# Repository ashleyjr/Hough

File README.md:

Hough
=====

Hough transform experiment

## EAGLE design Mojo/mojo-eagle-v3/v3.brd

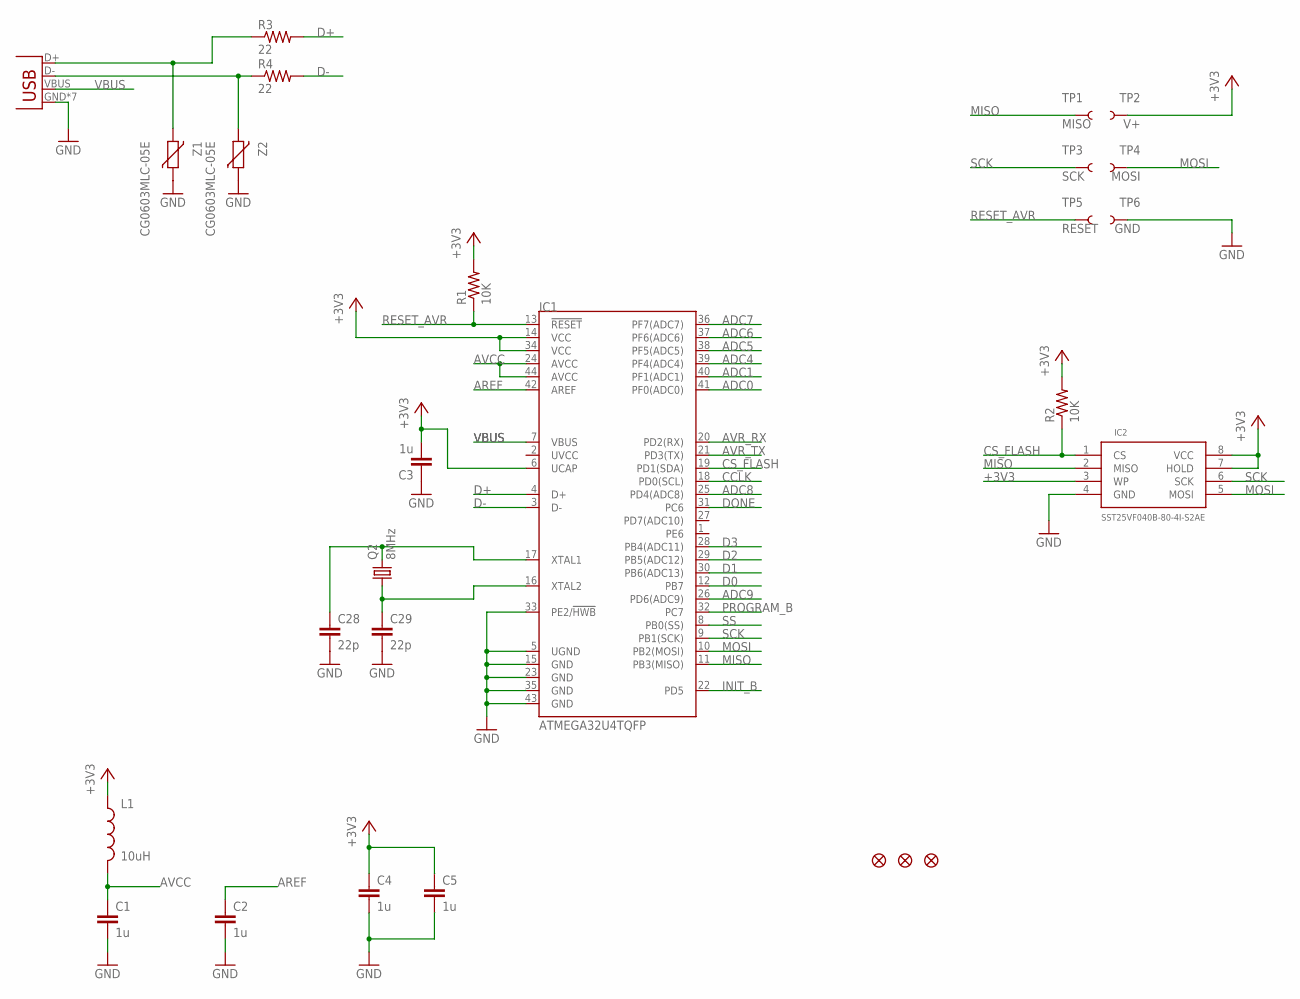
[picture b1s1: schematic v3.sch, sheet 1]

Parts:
C1, C2, C3, C4, C5: 1u; C0603K
C28, C29: 22p; C0603K
IC1: ATMEGA32U4TQFP; SPARKFUN-DIGITALIC_TQFP44
IC2: SST25VF040B-80-4I-S2AE; SO08-EIAJ
JP3, JP4, JP5: FIDUCIAL1X2; FIDUCIAL-1X2
L1: 10uH; 0603
Q2: 8MHz; ABM2
R1, R2: 10K; R0603
R3, R4: 22; R0603
TP1: MISO; PAD.03X.05
TP2: V+; PAD.03X.05
TP3: SCK; PAD.03X.05
TP4: MOSI; PAD.03X.05
TP5: RESET; PAD.03X.05
TP6: GND; PAD.03X.05
X1: USB-MICROB
Z1, Z2: CG0603MLC-05E; CT/CN0603

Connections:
+3V3: C3.2, C4.1, C5.1, IC1.6 (UCAP), IC1.14 (VCC), IC1.34 (VCC), IC2.3 (WP), IC2.7 (HOLD), IC2.8 (VCC), L1.1, R1.2, R2.2, TP2.P$1; also elsewhere on the board
ADC0: IC1.41 (PF0(ADC0)); also elsewhere on the board
ADC1: IC1.40 (PF1(ADC1)); also elsewhere on the board
ADC4: IC1.39 (PF4(ADC4)); also elsewhere on the board
ADC5: IC1.38 (PF5(ADC5)); also elsewhere on the board
ADC6: IC1.37 (PF6(ADC6)); also elsewhere on the board
ADC7: IC1.36 (PF7(ADC7)); also elsewhere on the board
ADC8: IC1.25 (PD4(ADC8)); also elsewhere on the board
ADC9: IC1.26 (PD6(ADC9)); also elsewhere on the board
AREF: C2.1, IC1.42 (AREF); also elsewhere on the board
AVCC: C1.1, IC1.24 (AVCC), IC1.44 (AVCC), L1.2
AVR_RX: IC1.20 (PD2(RX)); also elsewhere on the board
AVR_TX: IC1.21 (PD3(TX)); also elsewhere on the board
CCLK: IC1.18 (PD0(SCL)); also elsewhere on the board
CS_FLASH: IC1.19 (PD1(SDA)), IC2.1 (CS), R2.1
D0: IC1.12 (PB7); also elsewhere on the board
D1: IC1.30 (PB6(ADC13)); also elsewhere on the board
D2: IC1.29 (PB5(ADC12)); also elsewhere on the board
D3: IC1.28 (PB4(ADC11)); also elsewhere on the board
D+: IC1.4 (D+), R3.2
D-: IC1.3 (D-), R4.2
DONE: IC1.31 (PC6); also elsewhere on the board
GND: C1.2, C2.2, C3.1, C4.2, C5.2, C28.2, C29.2, IC1.5 (UGND), IC1.15 (GND), IC1.23 (GND), IC1.33 (PE2/!HWB), IC1.35 (GND), IC1.43 (GND), IC2.4 (GND), TP6.P$1, X1.GND, X1.P1 (GND), X1.P2 (GND), X1.P3 (GND), X1.P4 (GND), X1.P5 (GND), X1.P6 (GND), Z1.1, Z2.1; also elsewhere on the board
INIT_B: IC1.22 (PD5); also elsewhere on the board
MISO: IC1.11 (PB3(MISO)), IC2.2 (MISO), TP1.P$1; also elsewhere on the board
MOSI: IC1.10 (PB2(MOSI)), IC2.5 (MOSI), TP4.P$1; also elsewhere on the board
unnamed: R3.1, X1.D+, Z1.2
unnamed: R4.1, X1.D-, Z2.2
unnamed: C28.1, IC1.17 (XTAL1), Q2.P$2 (2)
unnamed: C29.1, IC1.16 (XTAL2), Q2.P$1 (1)
PROGRAM_B: IC1.32 (PC7); also elsewhere on the board
RESET_AVR: IC1.13 (!RESET), R1.1, TP5.P$1
SCK: IC1.9 (PB1(SCK)), IC2.6 (SCK), TP3.P$1; also elsewhere on the board
SS: IC1.8 (PB0(SS)); also elsewhere on the board
VBUS: IC1.7 (VBUS), X1.VBUS; also elsewhere on the board

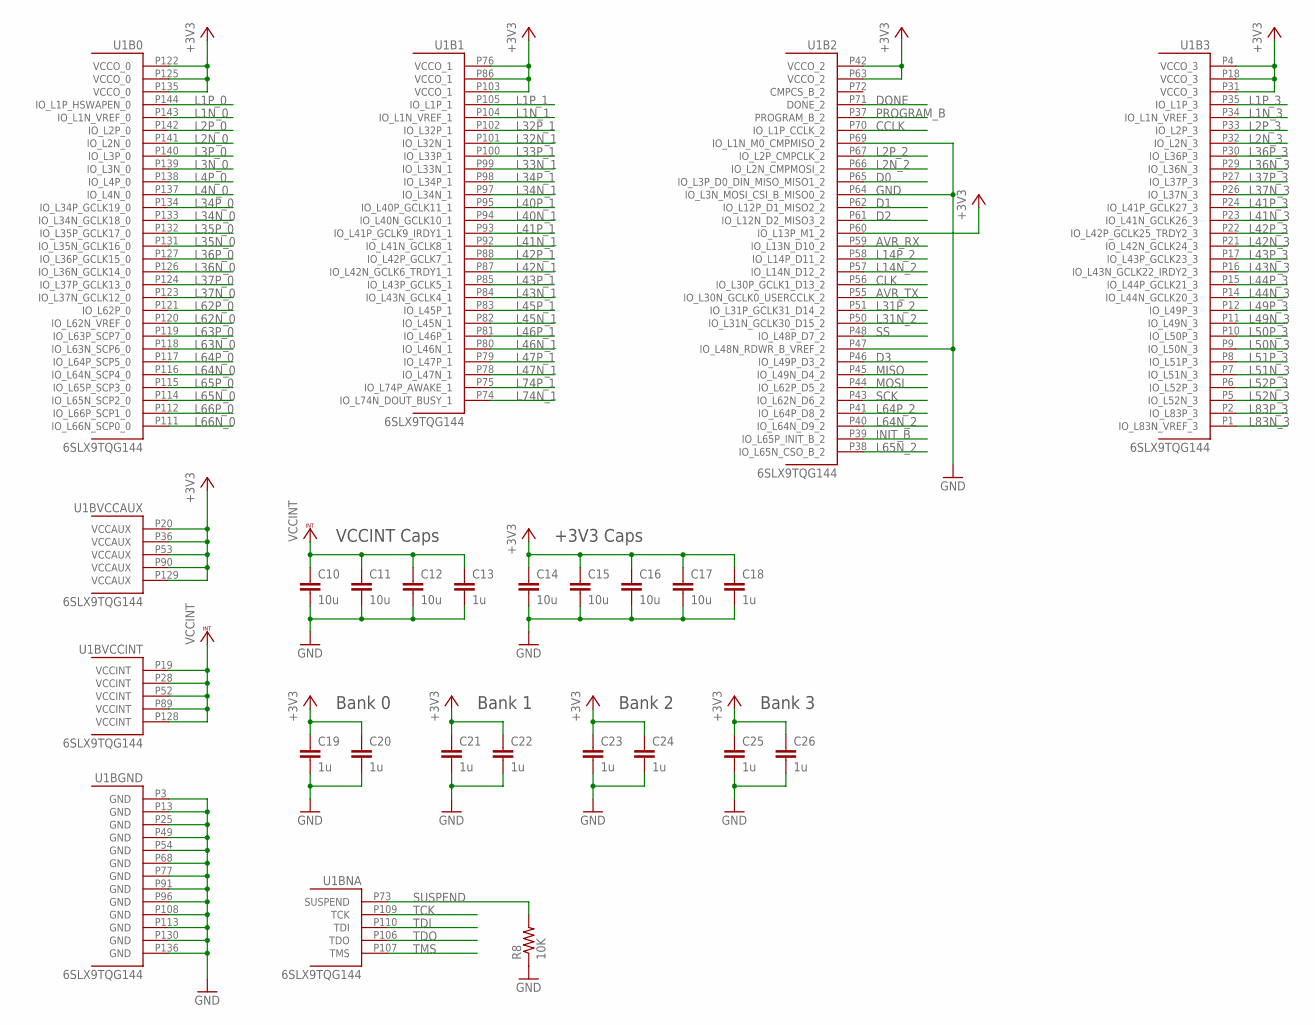
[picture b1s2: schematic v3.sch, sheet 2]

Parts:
C10, C11, C12, C14, C15, C16, C17: 10u; C0603K
C13, C18, C19, C20, C21, C22, C23, C24, C25, C26: 1u; C0603K
R8: 10K; R0603
U1: 6SLX9TQG144; TQ144

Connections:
+3V3: C14.1, C15.1, C16.1, C17.1, C18.1, C19.1, C20.1, C21.1, C22.1, C23.1, C24.1, C25.1, C26.1, U1.P4 (VCCO_3), U1.P18 (VCCO_3), U1.P20 (VCCAUX), U1.P31 (VCCO_3), U1.P36 (VCCAUX), U1.P42 (VCCO_2), U1.P53 (VCCAUX), U1.P60 (IO_L13P_M1_2), U1.P63 (VCCO_2), U1.P76 (VCCO_1), U1.P86 (VCCO_1), U1.P90 (VCCAUX), U1.P103 (VCCO_1), U1.P122 (VCCO_0), U1.P125 (VCCO_0), U1.P129 (VCCAUX), U1.P135 (VCCO_0); also elsewhere on the board
AVR_RX: U1.P59 (IO_L13N_D10_2); also elsewhere on the board
AVR_TX: U1.P55 (IO_L30N_GCLK0_USERCCLK_2); also elsewhere on the board
CCLK: U1.P70 (IO_L1P_CCLK_2); also elsewhere on the board
CLK: U1.P56 (IO_L30P_GCLK1_D13_2); also elsewhere on the board
D0: U1.P65 (IO_L3P_D0_DIN_MISO_MISO1_2); also elsewhere on the board
D1: U1.P62 (IO_L12P_D1_MISO2_2); also elsewhere on the board
D2: U1.P61 (IO_L12N_D2_MISO3_2); also elsewhere on the board
D3: U1.P46 (IO_L49P_D3_2); also elsewhere on the board
DONE: U1.P71 (DONE_2); also elsewhere on the board
GND: C10.2, C11.2, C12.2, C13.2, C14.2, C15.2, C16.2, C17.2, C18.2, C19.2, C20.2, C21.2, C22.2, C23.2, C24.2, C25.2, C26.2, R8.1, U1.P3 (GND), U1.P13 (GND), U1.P25 (GND), U1.P47 (IO_L48N_RDWR_B_VREF_2), U1.P49 (GND), U1.P54 (GND), U1.P64 (IO_L3N_MOSI_CSI_B_MISO0_2), U1.P68 (GND), U1.P69 (IO_L1N_M0_CMPMISO_2), U1.P77 (GND), U1.P91 (GND), U1.P96 (GND), U1.P108 (GND), U1.P113 (GND), U1.P130 (GND), U1.P136 (GND); also elsewhere on the board
INIT_B: U1.P39 (IO_L65P_INIT_B_2); also elsewhere on the board
L1N_0: U1.P143 (IO_L1N_VREF_0); also elsewhere on the board
L1N_1: U1.P104 (IO_L1N_VREF_1); also elsewhere on the board
L1N_3: U1.P34 (IO_L1N_VREF_3); also elsewhere on the board
L1P_0: U1.P144 (IO_L1P_HSWAPEN_0); also elsewhere on the board
L1P_1: U1.P105 (IO_L1P_1); also elsewhere on the board
L1P_3: U1.P35 (IO_L1P_3); also elsewhere on the board
L2N_0: U1.P141 (IO_L2N_0); also elsewhere on the board
L2N_2: U1.P66 (IO_L2N_CMPMOSI_2); also elsewhere on the board
L2N_3: U1.P32 (IO_L2N_3); also elsewhere on the board
L2P_0: U1.P142 (IO_L2P_0); also elsewhere on the board
L2P_2: U1.P67 (IO_L2P_CMPCLK_2); also elsewhere on the board
L2P_3: U1.P33 (IO_L2P_3); also elsewhere on the board
L3N_0: U1.P139 (IO_L3N_0); also elsewhere on the board
L3P_0: U1.P140 (IO_L3P_0); also elsewhere on the board
L4N_0: U1.P137 (IO_L4N_0); also elsewhere on the board
L4P_0: U1.P138 (IO_L4P_0); also elsewhere on the board
L14N_2: U1.P57 (IO_L14N_D12_2); also elsewhere on the board
L14P_2: U1.P58 (IO_L14P_D11_2); also elsewhere on the board
L31N_2: U1.P50 (IO_L31N_GCLK30_D15_2); also elsewhere on the board
L31P_2: U1.P51 (IO_L31P_GCLK31_D14_2); also elsewhere on the board
L32N_1: U1.P101 (IO_L32N_1); also elsewhere on the board
L32P_1: U1.P102 (IO_L32P_1); also elsewhere on the board
L33N_1: U1.P99 (IO_L33N_1); also elsewhere on the board
L33P_1: U1.P100 (IO_L33P_1); also elsewhere on the board
L34N_0: U1.P133 (IO_L34N_GCLK18_0); also elsewhere on the board
L34N_1: U1.P97 (IO_L34N_1); also elsewhere on the board
L34P_0: U1.P134 (IO_L34P_GCLK19_0); also elsewhere on the board
L34P_1: U1.P98 (IO_L34P_1); also elsewhere on the board
L35N_0: U1.P131 (IO_L35N_GCLK16_0); also elsewhere on the board
L35P_0: U1.P132 (IO_L35P_GCLK17_0); also elsewhere on the board
L36N_0: U1.P126 (IO_L36N_GCLK14_0); also elsewhere on the board
L36N_3: U1.P29 (IO_L36N_3); also elsewhere on the board
L36P_0: U1.P127 (IO_L36P_GCLK15_0); also elsewhere on the board
L36P_3: U1.P30 (IO_L36P_3); also elsewhere on the board
L37N_0: U1.P123 (IO_L37N_GCLK12_0); also elsewhere on the board
L37N_3: U1.P26 (IO_L37N_3); also elsewhere on the board
L37P_0: U1.P124 (IO_L37P_GCLK13_0); also elsewhere on the board
L37P_3: U1.P27 (IO_L37P_3); also elsewhere on the board
L40N_1: U1.P94 (IO_L40N_GCLK10_1); also elsewhere on the board
L40P_1: U1.P95 (IO_L40P_GCLK11_1); also elsewhere on the board
L41N_1: U1.P92 (IO_L41N_GCLK8_1); also elsewhere on the board
L41N_3: U1.P23 (IO_L41N_GCLK26_3); also elsewhere on the board
L41P_1: U1.P93 (IO_L41P_GCLK9_IRDY1_1); also elsewhere on the board
L41P_3: U1.P24 (IO_L41P_GCLK27_3); also elsewhere on the board
L42N_1: U1.P87 (IO_L42N_GCLK6_TRDY1_1); also elsewhere on the board
L42N_3: U1.P21 (IO_L42N_GCLK24_3); also elsewhere on the board
L42P_1: U1.P88 (IO_L42P_GCLK7_1); also elsewhere on the board
L42P_3: U1.P22 (IO_L42P_GCLK25_TRDY2_3); also elsewhere on the board
L43N_1: U1.P84 (IO_L43N_GCLK4_1); also elsewhere on the board
L43N_3: U1.P16 (IO_L43N_GCLK22_IRDY2_3); also elsewhere on the board
L43P_1: U1.P85 (IO_L43P_GCLK5_1); also elsewhere on the board
L43P_3: U1.P17 (IO_L43P_GCLK23_3); also elsewhere on the board
L44N_3: U1.P14 (IO_L44N_GCLK20_3); also elsewhere on the board
L44P_3: U1.P15 (IO_L44P_GCLK21_3); also elsewhere on the board
L45N_1: U1.P82 (IO_L45N_1); also elsewhere on the board
L45P_1: U1.P83 (IO_L45P_1); also elsewhere on the board
L46N_1: U1.P80 (IO_L46N_1); also elsewhere on the board
L46P_1: U1.P81 (IO_L46P_1); also elsewhere on the board
L47N_1: U1.P78 (IO_L47N_1); also elsewhere on the board
L47P_1: U1.P79 (IO_L47P_1); also elsewhere on the board
L49N_3: U1.P11 (IO_L49N_3); also elsewhere on the board
L49P_3: U1.P12 (IO_L49P_3); also elsewhere on the board
L50N_3: U1.P9 (IO_L50N_3); also elsewhere on the board
L50P_3: U1.P10 (IO_L50P_3); also elsewhere on the board
L51N_3: U1.P7 (IO_L51N_3); also elsewhere on the board
L51P_3: U1.P8 (IO_L51P_3); also elsewhere on the board
L52N_3: U1.P5 (IO_L52N_3); also elsewhere on the board
L52P_3: U1.P6 (IO_L52P_3); also elsewhere on the board
L62N_0: U1.P120 (IO_L62N_VREF_0); also elsewhere on the board
L62P_0: U1.P121 (IO_L62P_0); also elsewhere on the board
L63N_0: U1.P118 (IO_L63N_SCP6_0); also elsewhere on the board
L63P_0: U1.P119 (IO_L63P_SCP7_0); also elsewhere on the board
L64N_0: U1.P116 (IO_L64N_SCP4_0); also elsewhere on the board
L64N_2: U1.P40 (IO_L64N_D9_2); also elsewhere on the board
L64P_0: U1.P117 (IO_L64P_SCP5_0); also elsewhere on the board
L64P_2: U1.P41 (IO_L64P_D8_2); also elsewhere on the board
L65N_0: U1.P114 (IO_L65N_SCP2_0); also elsewhere on the board
L65N_2: U1.P38 (IO_L65N_CSO_B_2); also elsewhere on the board
L65P_0: U1.P115 (IO_L65P_SCP3_0); also elsewhere on the board
L66N_0: U1.P111 (IO_L66N_SCP0_0); also elsewhere on the board
L66P_0: U1.P112 (IO_L66P_SCP1_0); also elsewhere on the board
L74N_1: U1.P74 (IO_L74N_DOUT_BUSY_1); also elsewhere on the board
L74P_1: U1.P75 (IO_L74P_AWAKE_1); also elsewhere on the board
L83N_3: U1.P1 (IO_L83N_VREF_3); also elsewhere on the board
L83P_3: U1.P2 (IO_L83P_3); also elsewhere on the board
MISO: U1.P45 (IO_L49N_D4_2); also elsewhere on the board
MOSI: U1.P44 (IO_L62P_D5_2); also elsewhere on the board
PROGRAM_B: U1.P37 (PROGRAM_B_2); also elsewhere on the board
SCK: U1.P43 (IO_L62N_D6_2); also elsewhere on the board
SS: U1.P48 (IO_L48P_D7_2); also elsewhere on the board
SUSPEND: R8.2, U1.P73 (SUSPEND); also elsewhere on the board
TCK: U1.P109 (TCK); also elsewhere on the board
TDI: U1.P110 (TDI); also elsewhere on the board
TDO: U1.P106 (TDO); also elsewhere on the board
TMS: U1.P107 (TMS); also elsewhere on the board
VCCINT: C10.1, C11.1, C12.1, C13.1, U1.P19 (VCCINT), U1.P28 (VCCINT), U1.P52 (VCCINT), U1.P89 (VCCINT), U1.P128 (VCCINT); also elsewhere on the board

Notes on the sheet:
VCCINT Caps
+3V3 Caps
Bank 0
Bank 1
Bank 2
Bank 3

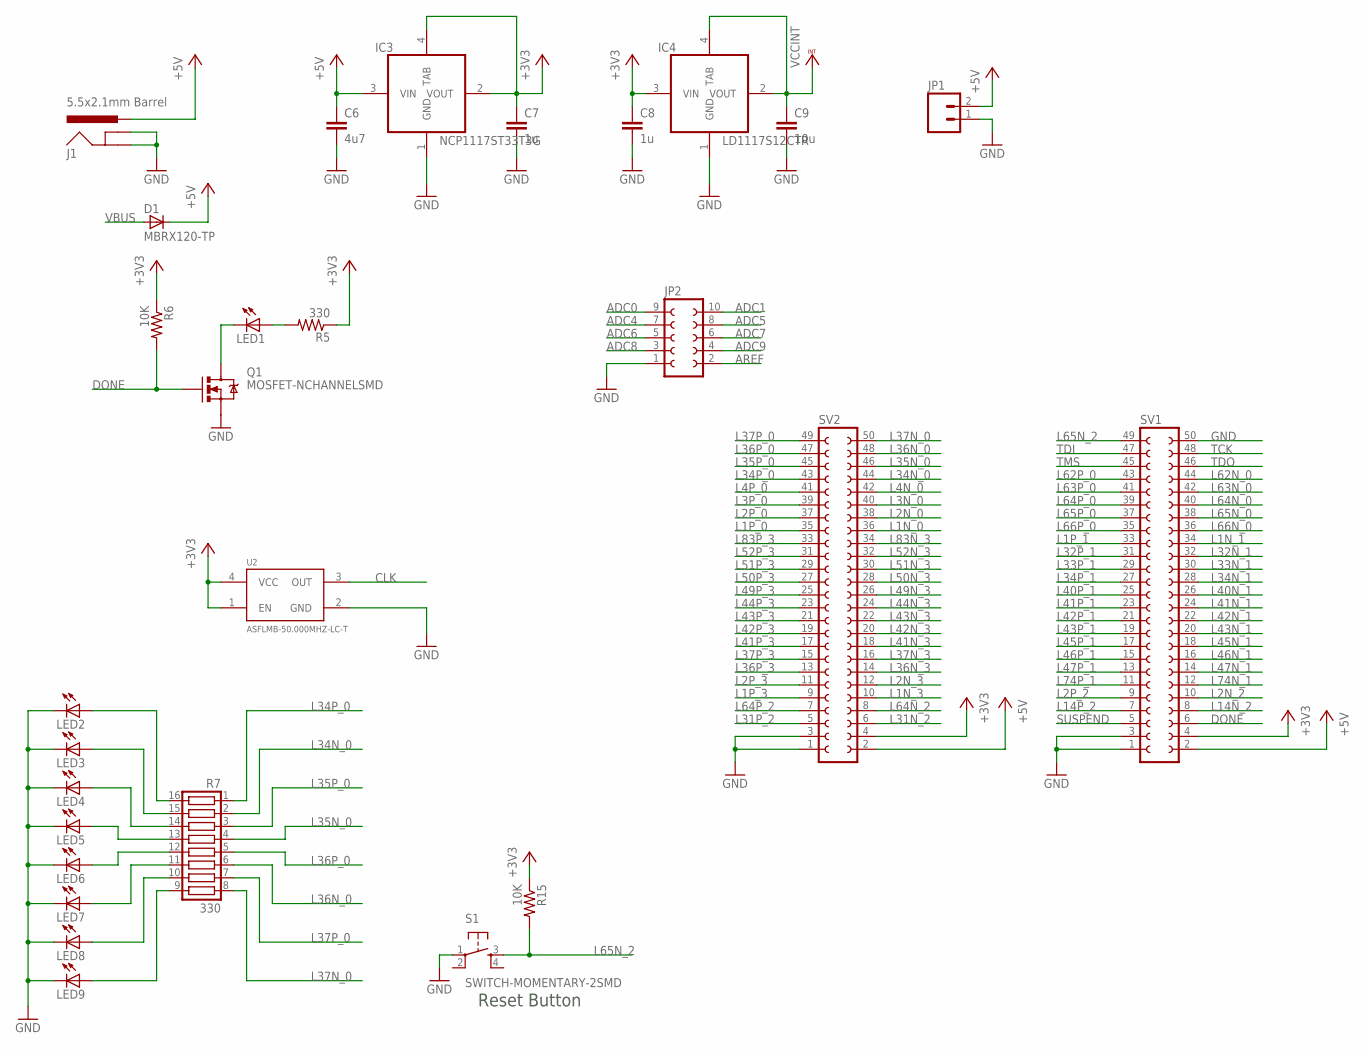
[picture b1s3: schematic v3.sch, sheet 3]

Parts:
C6: 4u7; C1206
C7, C8: 1u; C0603K
C9: 10u; C0603K
D1: MBRX120-TP; SOD123
IC3: NCP1117ST33T3G; SOT223
IC4: LD1117S12CTR; SOT223
J1: 5.5x2.1mm Barrel; POWER_JACK_SMD
JP1: M02PTH; 1X02
JP2: FE05-2
LED1, LED2, LED3, LED4, LED5, LED6, LED7, LED8, LED9: LED1206; LED-1206
Q1: MOSFET-NCHANNELSMD; SOT23-3
R5: 330; R0603
R6, R15: 10K; R0603
R7: 330; CTS743C163
S1: SWITCH-MOMENTARY-2SMD; TACTILE_SWITCH_SMD
SV1, SV2: FE25-2
U2: ASFLMB-50.000MHZ-LC-T; CRYSTAL-OSC-SMD-5X3

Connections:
+3V3: C7.1, C8.1, IC3.2 (VOUT), IC3.4 (TAB), IC4.3 (VIN), R5.1, R6.1, R15.1, SV1.4, SV2.4, U2.1 (EN), U2.4 (VCC); also elsewhere on the board
+5V: C6.1, D1.1 (C), IC3.3 (VIN), J1.VIN0 (PWR), JP1.2, SV1.2, SV2.2
ADC0: JP2.9; also elsewhere on the board
ADC1: JP2.10; also elsewhere on the board
ADC4: JP2.7; also elsewhere on the board
ADC5: JP2.8; also elsewhere on the board
ADC6: JP2.5; also elsewhere on the board
ADC7: JP2.6; also elsewhere on the board
ADC8: JP2.3; also elsewhere on the board
ADC9: JP2.4; also elsewhere on the board
AREF: JP2.2; also elsewhere on the board
CLK: U2.3 (OUT); also elsewhere on the board
DONE: Q1.1 (G), R6.2, SV1.6; also elsewhere on the board
GND: C6.2, C7.2, C8.2, C9.2, IC3.1 (GND), IC4.1 (GND), J1.GND (GNDBREAK), J1.P$4 (GND), JP1.1, JP2.1, LED2.C, LED3.C, LED4.C, LED5.C, LED6.C, LED7.C, LED8.C, LED9.C, Q1.2 (S), S1.1, SV1.1, SV1.3, SV1.50, SV2.1, SV2.3, U2.2 (GND); also elsewhere on the board
L1N_0: SV2.36; also elsewhere on the board
L1N_1: SV1.34; also elsewhere on the board
L1N_3: SV2.10; also elsewhere on the board
L1P_0: SV2.35; also elsewhere on the board
L1P_1: SV1.33; also elsewhere on the board
L1P_3: SV2.9; also elsewhere on the board
L2N_0: SV2.38; also elsewhere on the board
L2N_2: SV1.10; also elsewhere on the board
L2N_3: SV2.12; also elsewhere on the board
L2P_0: SV2.37; also elsewhere on the board
L2P_2: SV1.9; also elsewhere on the board
L2P_3: SV2.11; also elsewhere on the board
L3N_0: SV2.40; also elsewhere on the board
L3P_0: SV2.39; also elsewhere on the board
L4N_0: SV2.42; also elsewhere on the board
L4P_0: SV2.41; also elsewhere on the board
L14N_2: SV1.8; also elsewhere on the board
L14P_2: SV1.7; also elsewhere on the board
L31N_2: SV2.6; also elsewhere on the board
L31P_2: SV2.5; also elsewhere on the board
L32N_1: SV1.32; also elsewhere on the board
L32P_1: SV1.31; also elsewhere on the board
L33N_1: SV1.30; also elsewhere on the board
L33P_1: SV1.29; also elsewhere on the board
L34N_0: R7.2, SV2.44; also elsewhere on the board
L34N_1: SV1.28; also elsewhere on the board
L34P_0: R7.1, SV2.43; also elsewhere on the board
L34P_1: SV1.27; also elsewhere on the board
L35N_0: R7.4, SV2.46; also elsewhere on the board
L35P_0: R7.3, SV2.45; also elsewhere on the board
L36N_0: R7.6, SV2.48; also elsewhere on the board
L36N_3: SV2.14; also elsewhere on the board
L36P_0: R7.5, SV2.47; also elsewhere on the board
L36P_3: SV2.13; also elsewhere on the board
L37N_0: R7.8, SV2.50; also elsewhere on the board
L37N_3: SV2.16; also elsewhere on the board
L37P_0: R7.7, SV2.49; also elsewhere on the board
L37P_3: SV2.15; also elsewhere on the board
L40N_1: SV1.26; also elsewhere on the board
L40P_1: SV1.25; also elsewhere on the board
L41N_1: SV1.24; also elsewhere on the board
L41N_3: SV2.18; also elsewhere on the board
L41P_1: SV1.23; also elsewhere on the board
L41P_3: SV2.17; also elsewhere on the board
L42N_1: SV1.22; also elsewhere on the board
L42N_3: SV2.20; also elsewhere on the board
L42P_1: SV1.21; also elsewhere on the board
L42P_3: SV2.19; also elsewhere on the board
L43N_1: SV1.20; also elsewhere on the board
L43N_3: SV2.22; also elsewhere on the board
L43P_1: SV1.19; also elsewhere on the board
L43P_3: SV2.21; also elsewhere on the board
L44N_3: SV2.24; also elsewhere on the board
L44P_3: SV2.23; also elsewhere on the board
L45N_1: SV1.18; also elsewhere on the board
L45P_1: SV1.17; also elsewhere on the board
L46N_1: SV1.16; also elsewhere on the board
L46P_1: SV1.15; also elsewhere on the board
L47N_1: SV1.14; also elsewhere on the board
L47P_1: SV1.13; also elsewhere on the board
L49N_3: SV2.26; also elsewhere on the board
L49P_3: SV2.25; also elsewhere on the board
L50N_3: SV2.28; also elsewhere on the board
L50P_3: SV2.27; also elsewhere on the board
L51N_3: SV2.30; also elsewhere on the board
L51P_3: SV2.29; also elsewhere on the board
L52N_3: SV2.32; also elsewhere on the board
L52P_3: SV2.31; also elsewhere on the board
L62N_0: SV1.44; also elsewhere on the board
L62P_0: SV1.43; also elsewhere on the board
L63N_0: SV1.42; also elsewhere on the board
L63P_0: SV1.41; also elsewhere on the board
L64N_0: SV1.40; also elsewhere on the board
L64N_2: SV2.8; also elsewhere on the board
L64P_0: SV1.39; also elsewhere on the board
L64P_2: SV2.7; also elsewhere on the board
L65N_0: SV1.38; also elsewhere on the board
L65N_2: R15.2, S1.3, SV1.49; also elsewhere on the board
L65P_0: SV1.37; also elsewhere on the board
L66N_0: SV1.36; also elsewhere on the board
L66P_0: SV1.35; also elsewhere on the board
L74N_1: SV1.12; also elsewhere on the board
L74P_1: SV1.11; also elsewhere on the board
L83N_3: SV2.34; also elsewhere on the board
L83P_3: SV2.33; also elsewhere on the board
unnamed: LED1.A, R5.2
unnamed: LED1.C, Q1.3 (D)
unnamed: LED2.A, R7.16
unnamed: LED3.A, R7.15
unnamed: LED4.A, R7.14
unnamed: LED5.A, R7.13
unnamed: LED6.A, R7.12
unnamed: LED7.A, R7.11
unnamed: LED8.A, R7.10
unnamed: LED9.A, R7.9
SUSPEND: SV1.5; also elsewhere on the board
TCK: SV1.48; also elsewhere on the board
TDI: SV1.47; also elsewhere on the board
TDO: SV1.46; also elsewhere on the board
TMS: SV1.45; also elsewhere on the board
VBUS: D1.2 (A); also elsewhere on the board
VCCINT: C9.1, IC4.2 (VOUT), IC4.4 (TAB); also elsewhere on the board

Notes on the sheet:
Reset Button

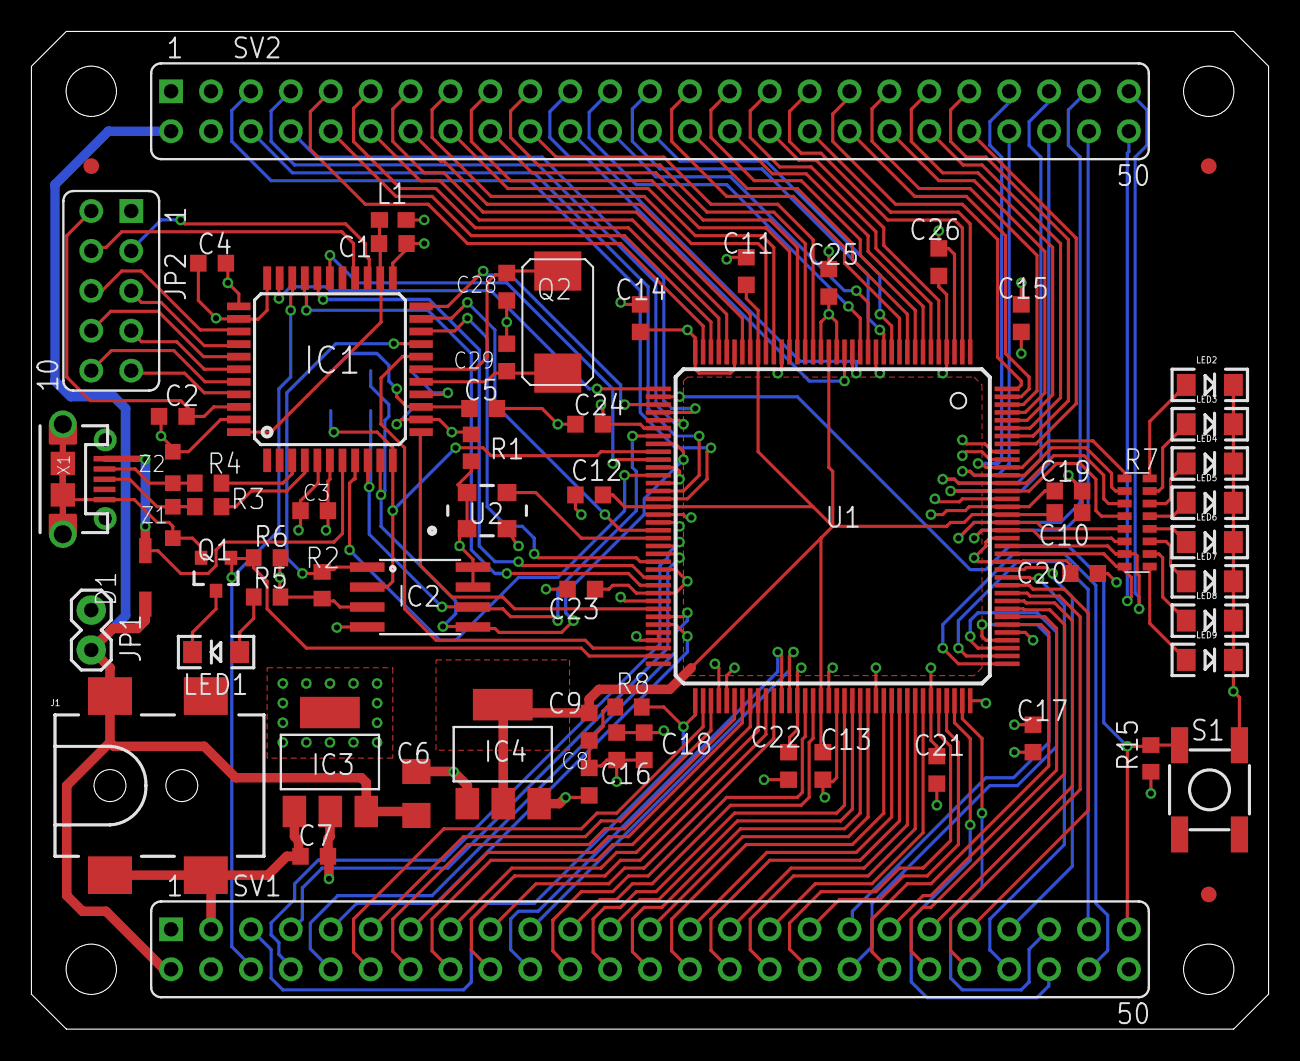
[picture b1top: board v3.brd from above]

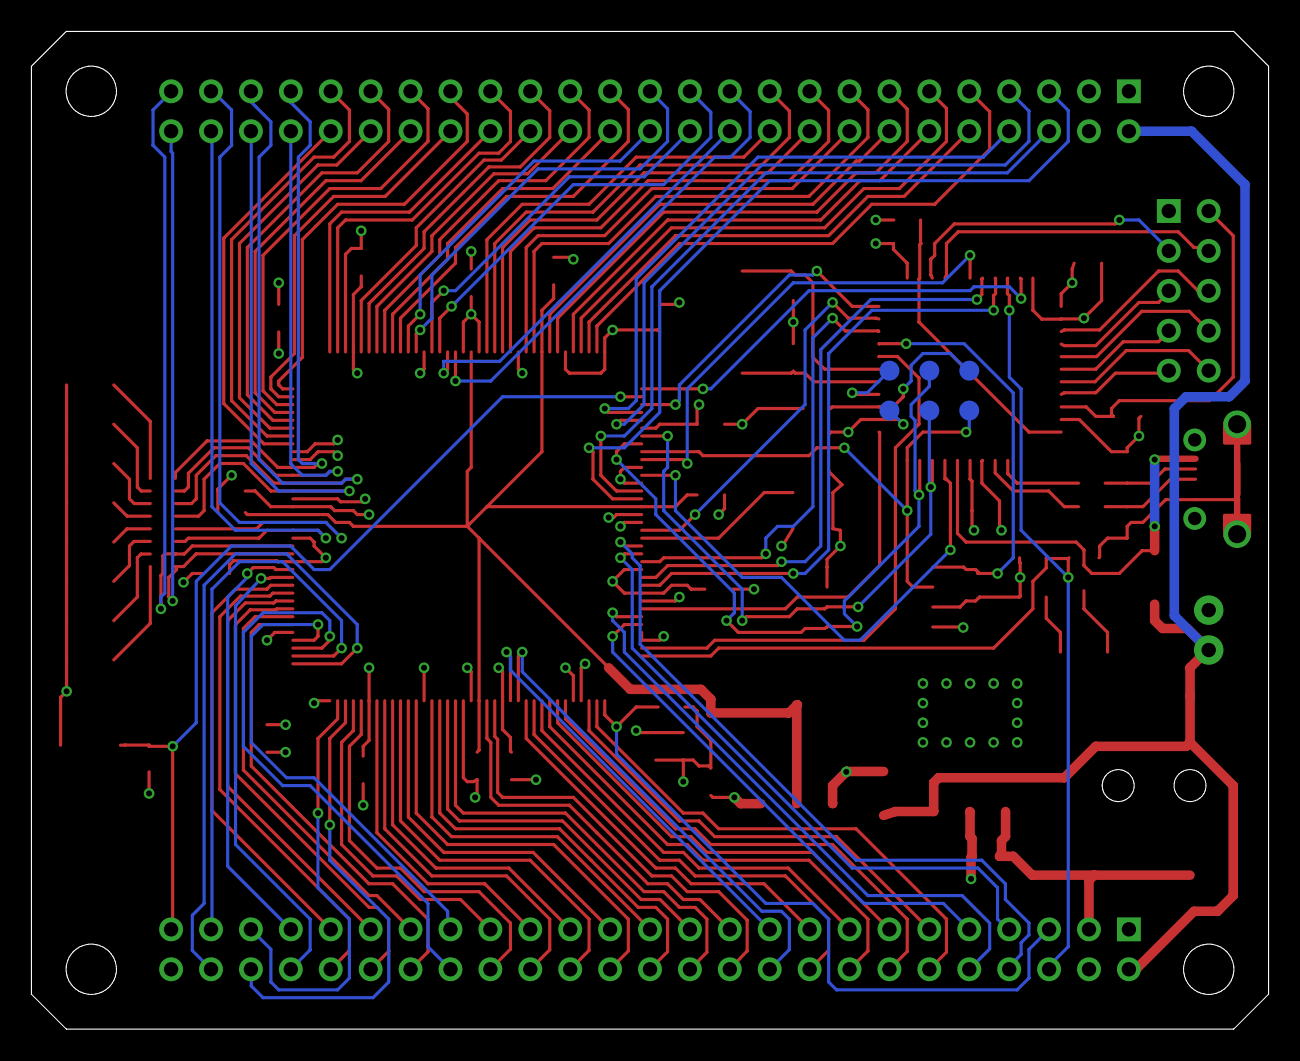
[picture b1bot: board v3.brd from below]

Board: 4 copper layers, 78.7 x 63.5 mm, 74 parts (6 on the bottom side), 138 nets.

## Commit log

2014-09-10 first play
2014-09-10 move to hw
2014-09-10 remove old
2014-09-10 folder for images
2014-09-10 remove old images
2014-09-10 read and writing an image
2014-09-11 out handler
2014-09-11 edge detect module begins
2014-09-12 sobel working
2014-09-12 iverilog on windows
2014-09-12 iverilog batch and cirle stuff
2014-09-12 clean up of unwanted files
2014-09-14 add circle
2014-09-14 edge script is out
2014-09-14 shell script
2014-09-19 try modelling in c
2014-09-20 c image op kernel setup
2014-09-20 wrong file loading
2014-09-20 issue with sixe of images
2014-09-21 sobel working??
2014-09-21 sobel works
2014-09-21 sobel in hw, need to comare
2014-09-22 reduced buffer requirements to 6 bits for a pixel
2014-09-23 deal with border arodun sobel output
2014-09-25 using buffers to realign the with coordinates
2014-09-25 only need lines in hough
2014-09-25 line works but needs a better approach
2014-10-05 cam on rpi and modelling with c
2014-11-22 python runsim
2014-11-22 cleaned up images
2014-11-29 first synthesis changes
2014-11-29 some hw bits
2014-11-30 started shield

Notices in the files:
parts and their libraries:
SparkFun-Connectors: Licensing: CC v3.0 Share-Alike You are welcome to use this library for commercial purposes.
